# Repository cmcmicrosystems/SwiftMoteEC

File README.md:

# SwiftMote-Electrochemical Sensor Platform

## Acknowledgement

The hardware and software of the SwiftMoteEC was developed by CMC Microsystems in collaboration with Dr. Phillippe Dauphin Ducharme and his team at Université de Sherbrooke’s Department of Chemistry and Abaxial Medical, as part of the Acuité Québec Consortium.

---

 <br>
Figure 1: SwiftMoteEC Hardware Prototype
<br><br>

  <br>
Figure 2: SwiftMoteEC Block Diagram
<br><br>

SwiftMote-Electrochemical Sensor Platform is a small, wireless (BLE) platform designed for electrochemical experiments that require free movement of the sensing platform.

The platform features:
* ST BlueNRG-LP Bluetooth Low Energy microcontroller
  * 256kB flash memory
  * Expansion ports with 4x 12-bit ADC and I2C
* Analog Devices AD5941 potentiostat amplifer with 16-bit ADC and 12-bit DAC
* Host PC application to receive and store sensor data

The platform hardware and software are open and modifiable for end user applications. CMC has limited hardware samples available for demonstration and evaluation. Contact us for availability and pricing.

## Repository

This repo contains hardware design files and demonstration application software to manufacture the existing platform or modify it for specific user needs:
> /hardware : printed circuit board development and manufacturing of prototype hardware

> /software : demonstration application for Server (SwiftMoteEC) and Client (Windows PC)

## Getting Started

Instructions to setup and run a demonstration application is provided in the [software README.md](/software/README.md).

## Support

CMC can assist, from answering technical enquiries, to helping with installation and setup, to providing consulting services to customize the platform for your needs. If you have questions:

* Consult [Known_Issues.md](Known_Issues.md) for any outstanding technical notes and workarounds
* Submit an Issue in the repository
* CMC Subscribers: submit support questions through CMC's [Online Support Form](https://www.cmc.ca/support/)
* Contact [lab@cmc.ca](mailto:lab@cmc.ca) for further enquiries

## Additional Resources

[CMC SwiftMote Product Page](https://www.cmc.ca/swiftmote-iot-customizable-sensor-platform/)

For ST BlueNRG-LP:
* [Product information, documentation, and support](https://www.st.com/en/wireless-connectivity/bluenrg-lp.html)
* [Evaluation Tool Software](https://www.st.com/en/embedded-software/stsw-bnrglp-dk.html)

For Analog Devices AD5940/AD5941:
* [Product information, documentation, and support](https://www.analog.com/en/products/ad5940.html)
* [AD5940 Code Examples](https://github.com/analogdevicesinc/ad5940-examples)

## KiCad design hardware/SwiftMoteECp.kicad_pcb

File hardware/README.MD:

# Acknowledgement
The hardware and software of the SwiftMoteEC was developed by CMC Microsystems in collaboration with Dr. Phillippe Dauphin Ducharme and his team at Université de Sherbrooke’s Department of Chemistry and Abaxial Medical,  as part of the Acuité Québec Consortium.

# SwiftMoteECp_HW Repository
This repo is for development of the prototype hardware.  

Directories:  
> ./		: Project files including the schematic and printed circuit board  
>> /documentation	: A brief overview of power and programming  
>> /graphics	: A block diagram and photos of SwiftMote-Electrochemical  
>> /libraries     	: KiCad project related libraries including part symbols and footprints  
>> /licenses	: All hardware-related licenses  
>> /manufacturing	: All necessary files to manufacture the board.  Subdirectories include:  
>>>    /Bill_of_Materials : Bill of Materials (BoM) used to manufacture the first version of the board  
>>>    /Drill_Files	: Mechanical drill files  
>>>    /Instructions	: Special instructions to be provided to the board manufacturer  
>>>    /Plots	: Gerber files  
>>>    /Stackup	: Board stackup  
>>>    /XY_Position_Files : Orientation of the parts on the board  

Attention: 
1. Expansion header J2 was incorrectly specified (only 9-pins loaded, need all 10).  Change MPN FTSH-105-01-L-DV-007-P to FTSH-105-01-L-DV-P (Digikey PN# SAM8910-ND). You need to make this modification to the Bill of Materials before sending to manufacturing.
2. Capacitor C16 was changed to 10uF, MPN C0402C106M9PACTU , update the BoM.

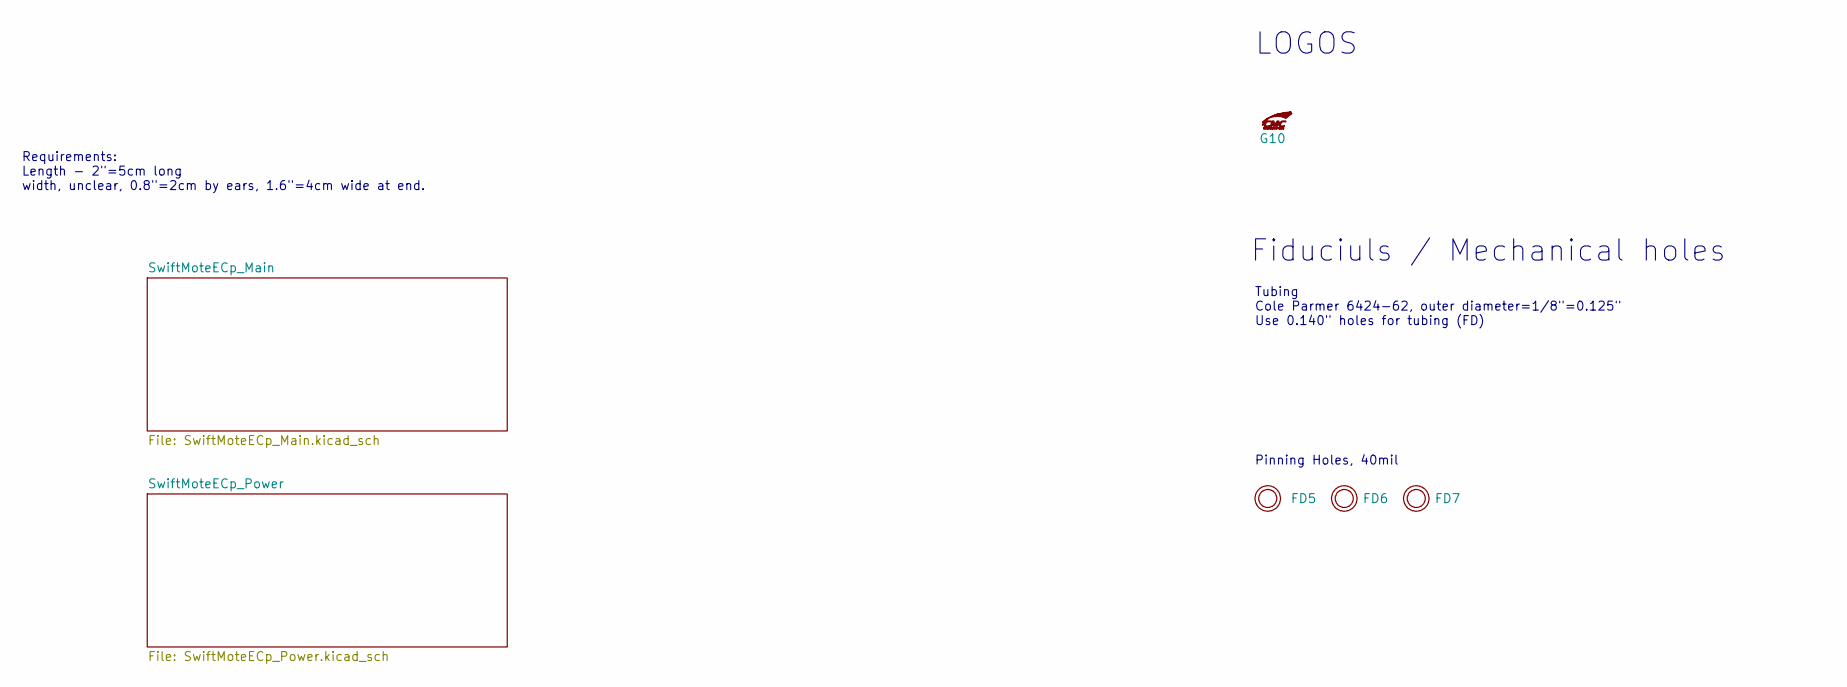
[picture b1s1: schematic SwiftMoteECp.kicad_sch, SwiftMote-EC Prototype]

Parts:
FD5, FD6, FD7: Pinning_NPTH_40mil
G10: CMC_White_Logo_180x110mil

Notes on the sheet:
Tubing Cole Parmer 6424-62, outer diameter=1/8"=0.125" Use 0.140" holes for tubing (FD)
Requirements: Length - 2"=5cm long width, unclear, 0.8"=2cm by ears, 1.6"=4cm wide at end.
LOGOS
Fiduciuls / Mechanical holes
Pinning Holes, 40mil

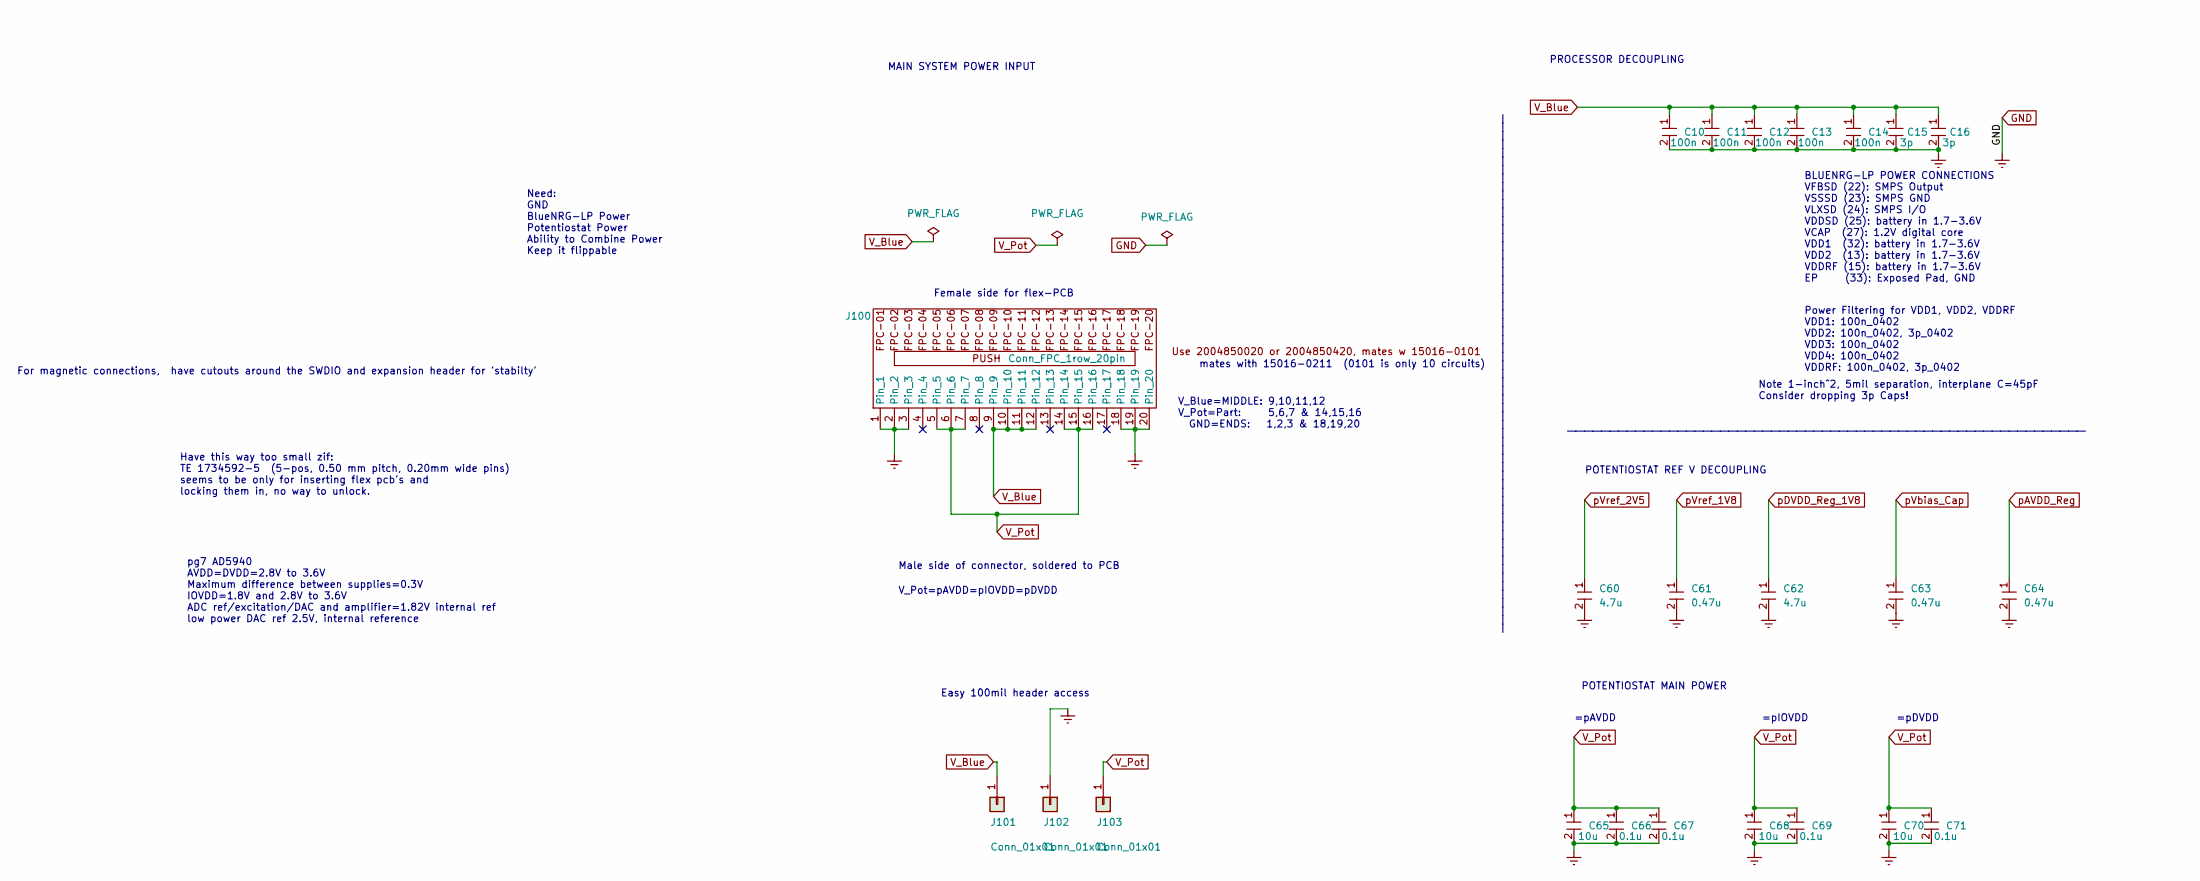
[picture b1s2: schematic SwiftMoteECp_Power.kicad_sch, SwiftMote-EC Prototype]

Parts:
C10, C11, C12, C13, C14: 100n; C_0402_1005Metric; Voltage 25V; Manufacturer PN GCM155R71E104KE02D; Digikey PN 490-16431-1-ND
C15, C16: 3p; C_0402_1005Metric; Voltage 50V; Manufacturer PN GCM1555C1H3R0BA16D; Digikey PN 490-14421-1-ND
C60, C62: 4.7u; C_0603_1608Metric; Voltage 16V; Manufacturer PN GRM188Z71C475KE21J; Digikey PN 490-GRM188Z71C475KE21JCT-ND
C61, C63, C64: 0.47u; C_0402_1005Metric; Voltage 10V; Manufacturer PN GRM155R71A474KE01D; Digikey PN 490-14366-1-ND
C65, C68: 10u; C_0805_2012Metric; Voltage 10V; Manufacturer PN GRM21BR71A106KA73L; Digikey PN 490-10516-1-ND
C66, C67, C69, C71: 0.1u; C_0402_1005Metric; Voltage 50V; Manufacturer PN GRM155R71H104KE14J; Digikey PN 490-13342-1-ND
C70: 10u; R_0805_2012Metric; Voltage 10V; Manufacturer PN GRM21BR71A106KA73L; Digikey PN 490-10516-1-ND
J100: Conn_FPC_1row_20pin; Molex_EasyOn_FFCFPC_2004850020; Manufacturer PN 2004850020; Digikey PN 900-2004850020TR-ND
J101, J102, J103: Conn_01x01; PinHeader_1x01_P2.54mm_Vertical; Manufacturer PN TSW-101-08-G-S; Digikey PN SAM1038-01-ND

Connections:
GND: C10.2, C11.2, C12.2, C13.2, C14.2, C15.2, C16.2, C60.2, C61.2, C62.2, C63.2, C64.2, C65.2, C66.2, C67.2, C68.2, C69.2, C70.2, C71.2, J100.1, J100.2, J100.3, J100.18, J100.19, J100.20, J102.1; also elsewhere on the board
V_Blue: C10.1, C11.1, C12.1, C13.1, C14.1, C15.1, C16.1, J100.9, J100.10, J100.11, J100.12, J101.1; also elsewhere on the board
V_Pot: C65.1, C66.1, C67.1, C68.1, C69.1, C70.1, C71.1, J100.5, J100.6, J100.7, J100.14, J100.15, J100.16, J103.1; also elsewhere on the board
pAVDD_Reg: C64.1; also elsewhere on the board
pDVDD_Reg_1V8: C62.1; also elsewhere on the board
pVbias_Cap: C63.1; also elsewhere on the board
pVref_1V8: C61.1; also elsewhere on the board
pVref_2V5: C60.1; also elsewhere on the board

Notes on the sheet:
Male side of connector, soldered to PCB
=pIOVDD
pg7 AD5940 AVDD=DVDD=2.8V to 3.6V Maximum difference between supplies=0.3V IOVDD=1.8V and 2.8V to 3.6V ADC ref/excitation/DAC and amplifier=1.82V internal ref low power DAC ref 2.5V, internal reference
_____________________________________________________________
Easy 100mil header access
Power Filtering for VDD1, VDD2, VDDRF VDD1: 100n_0402 VDD2: 100n_0402, 3p_0402 VDD3: 100n_0402 VDD4: 100n_0402 VDDRF: 100n_0402, 3p_0402
PROCESSOR DECOUPLING
Have this way too small zif: TE 1734592-5 (5-pos, 0.50 mm pitch, 0.20mm wide pins) seems to be only for inserting flex pcb's and locking them in, no way to unlock.
For magnetic connections, have cutouts around the SWDIO and expansion header for 'stabilty'
mates with 15016-0211 (0101 is only 10 circuits)
BLUENRG-LP POWER CONNECTIONS VFBSD (22): SMPS Output VSSSD (23): SMPS GND VLXSD (24): SMPS I/O VDDSD (25): battery in 1.7-3.6V VCAP (27): 1.2V digital core VDD1 (32): battery in 1.7-3.6V VDD2 (13): battery in 1.7-3.6V VDDRF (15): battery in 1.7-3.6V EP (33): Exposed Pad, GND
V_Blue=MIDDLE: 9,10,11,12 V_Pot=Part: 5,6,7 & 14,15,16 GND=ENDS: 1,2,3 & 18,19,20
Female side for flex-PCB
POTENTIOSTAT MAIN POWER
POTENTIOSTAT REF V DECOUPLING
=pDVDD
Note 1-inch^2, 5mil separation, interplane C=45pF Consider dropping 3p Caps!
V_Pot=pAVDD=pIOVDD=pDVDD
Need: GND BlueNRG-LP Power Potentiostat Power Ability to Combine Power Keep it flippable
=pAVDD
MAIN SYSTEM POWER INPUT

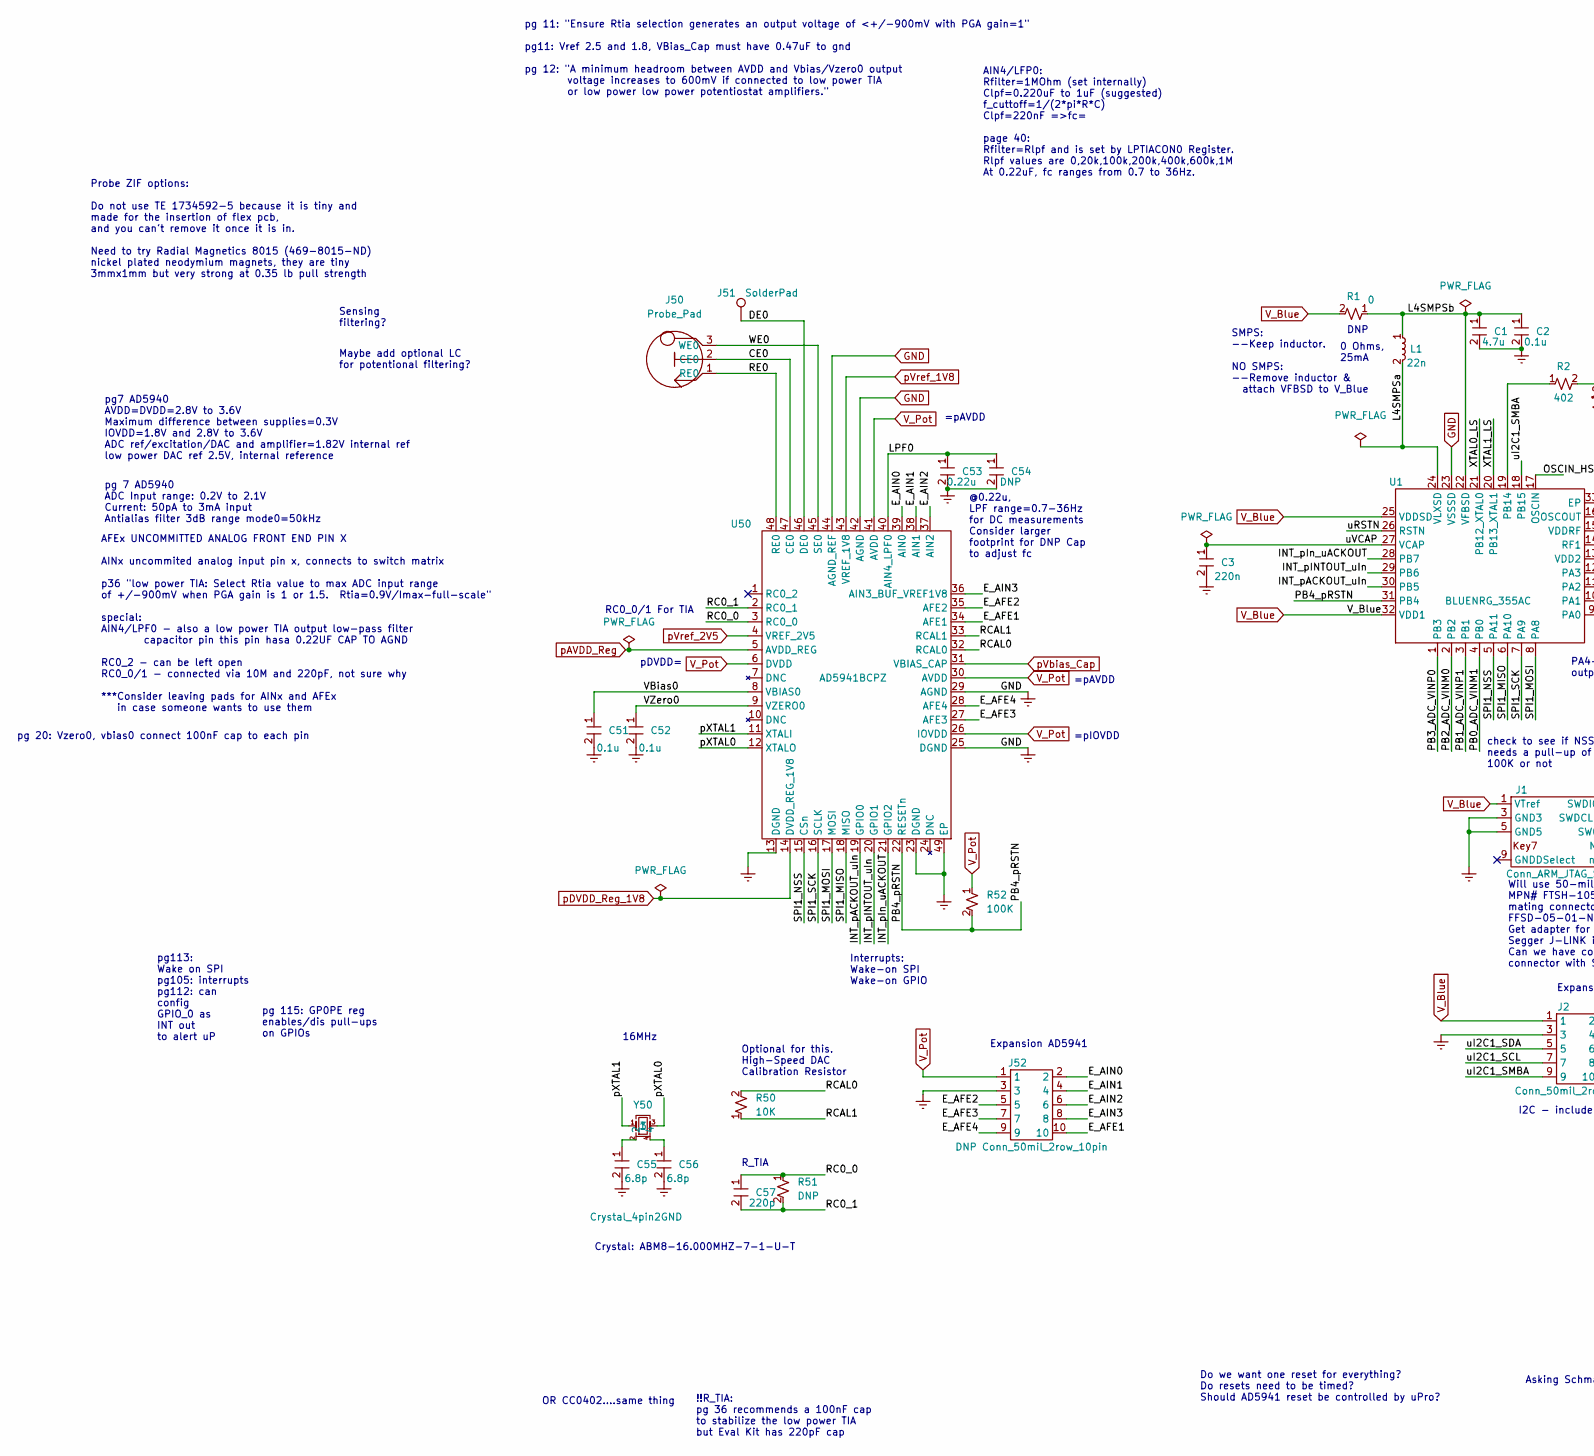
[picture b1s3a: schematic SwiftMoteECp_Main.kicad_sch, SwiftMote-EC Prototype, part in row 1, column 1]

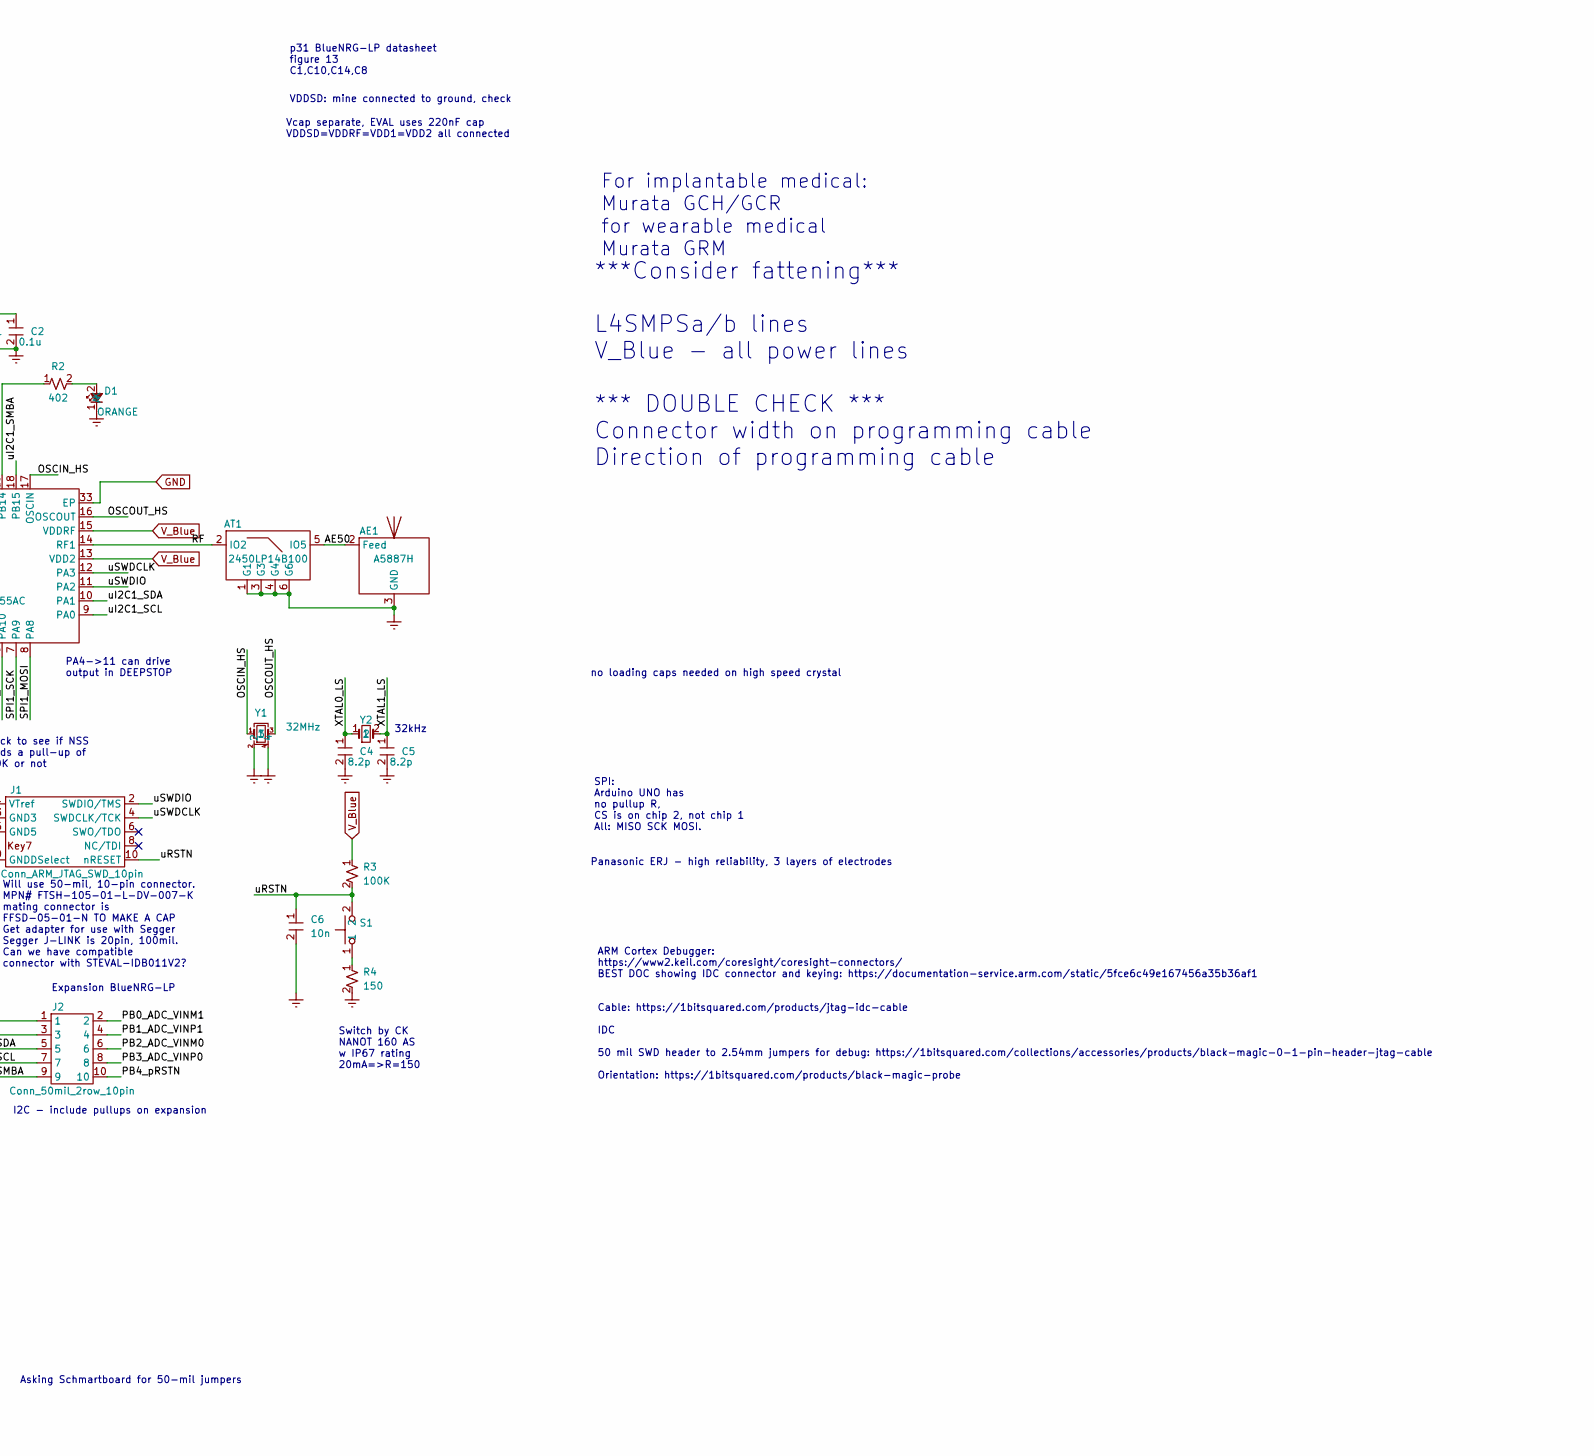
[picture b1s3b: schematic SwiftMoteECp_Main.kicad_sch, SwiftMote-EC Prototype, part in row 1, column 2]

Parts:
AE1: A5887H; RUFA_RT_A5887H; Manufacturer PN A5887H; Digikey PN 627-1127-1-ND
AT1: 2450LP14B100; JT_LPF_Bluetooth_2450LP14B100; Manufacturer PN 2450LP14B100T; Digikey PN 712-1130-1-ND
C1: 4.7u; C_0402_1005Metric; Voltage 16V; Manufacturer PN CL05A475MO5NUNC; Digikey PN 1276-6836-1-ND
C2, C51, C52: 0.1u; C_0402_1005Metric; Voltage 25V; Manufacturer PN C1005X7R1E104K050BB; Digikey PN 445-7348-1-ND
C3: 220n; R_0402_1005Metric; Voltage 25V; Manufacturer PN CGA2B3X7R1E224K050BB; Digikey PN 445-174424-1-ND
C4, C5: 8.2p; C_0201_0603Metric; Voltage 50V; Manufacturer PN GRM0335C1H8R2DA01D; Digikey PN 490-6133-1-ND
C6: 10n; C_0402_1005Metric; Voltage 25V; Manufacturer PN GRM1555C1E103GE01D; Digikey PN 490-GRM1555C1E103GE01DCT-ND
C53: 0.22u; C_0402_1005Metric_Pad0.74x0.62mm_HandSolder; Voltage 25V; Manufacturer PN GCM155R71C224KE02D; Digikey PN 490-10671-1-ND
C54: DNP; C_0402_1005Metric_Pad0.74x0.62mm_HandSolder; Voltage 25V; Manufacturer PN GCM155R71C224KE02D; Digikey PN 490-10671-1-ND
C55, C56: 6.8p; C_0402_1005Metric; Voltage 25V; Manufacturer PN C0402C689D3GAC7867; Digikey PN 399-15342-1-ND
C57: 220p; C_0402_1005Metric_Pad0.74x0.62mm_HandSolder; Voltage 25V; Manufacturer PN CC0402JRNPO8BN221; Digikey PN 311-1026-1-ND
D1: ORANGE; LED_0603_1608Metric_Pad1.05x0.95mm_HandSolder; Manufacturer PN XZCM2MOK53WA-1VF; Digikey PN 1497-XZCM2MOK53WA-1VFCT-ND
J1: Conn_ARM_JTAG_SWD_10pin; FTSH_10pin_2rows_50milPitch; Manufacturer PN FTSH-105-01-l-DV-007-K; Digikey PN SAM9438-ND
J2: Conn_50mil_2row_10pin; BlueExp_10pin_2rows_50milPitch; Manufacturer PN FTSH-105-01-l-DV-007-P; Digikey PN FTSH-105-01-L-DV-007-P-ND
J50: Probe_Pad; ProbePad_Magnetic_5x5mm; Manufacturer PN DNP; Digikey PN DNP
J51: SolderPad; Pad_5x5mm; Manufacturer PN DNP
J52: DNP Conn_50mil_2row_10pin; Conn_10pin_2rows_50milPitch; Manufacturer PN FTSH-105-01-l-DV-007-P; Digikey PN FTSH-105-01-L-DV-007-P-ND
L1: 22n; L_SMD_0402_1005Metric_Pad0.77x0.64mm_HandSolder; Manufacturer PN LQG15HS22NG02D; Digikey PN 490-LQG15HS22NG02DCT-ND
R1: 0; R_0402_1005Metric_Pad0.72x0.64mm_HandSolder; Manufacturer PN ERJ-U020R00X; Digikey PN 10-ERJ-U020R00XCT-ND
R2: 402; R_0402_1005Metric_Pad0.72x0.64mm_HandSolder; Manufacturer PN ERJ-2RKF4020X; Digikey PN P402LCT-ND
R3, R52: 100K; R_0402_1005Metric; Voltage 50V; Manufacturer PN CR0402-FX-1003GLF; Digikey PN CR0402-FX-1003GLFCT-ND
R4: 150; R_0402_1005Metric; Voltage 50V; Manufacturer PN ERJ-U02F1500X; Digikey PN 10-ERJ-U02F1500XCT-ND
R50: 10K; R_0603_1608Metric_Pad0.98x0.95mm_HandSolder; Voltage 75V; Tolerance 0.1%; Manufacturer PN ERA-3ARB103V; Digikey PN P10KBDCT-ND
R51: DNP; R_0402_1005Metric_Pad0.72x0.64mm_HandSolder
S1: Switch_SPST_NO; CuK_NanoT_AS; Manufacturer PN NANOT 160 AS; Digikey PN 108-NANOT160ASCT-ND
U1: BLUENRG_355AC; ST_BlueNRG_LP_QFN-32-1EP_5x5mm_P0.5mm_EP3.6x3.6mm; Manufacturer PN BLUENRG-355AT; Digikey PN 497-BLUENRG-355ATCT-ND
U50: AD5941BCPZ; AD5941BCPZ_LFCSP-48-1EP_7x7mm_P0.5mm_EP4.1x4.1mm; Manufacturer PN AD5941BCPZ; Digikey PN 505-AD5941BCPZ-ND
Y1: 32MHz; Crystal_SMD_2016-4Pin_2.0x1.6mm_sm; Manufacturer PN NX2016SA-32MHZ-EXS00A-CS11213; Digikey PN 644-1376-1-ND
Y2: Crystal_2pin; Crystal_SMD_2012-2Pin_2.0x1.2mm_sm; Manufacturer PN NX2012SA-32.768KHZ-EXS00A-MU00530; Digikey PN 644-1354-1-ND
Y50: Crystal_4pin2GND; Crystal_SMD_3225-4Pin_3.2x2.5mm; Manufacturer PN ABM8-16.000MHZ-7-1-U-T; Digikey PN 535-13466-1-ND

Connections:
/RatKit_Main/AE50: AE1.2 (Feed), AT1.5 (IO5)
/RatKit_Main/CE0: J50.2 (CE0), U50.47 (CE0)
/RatKit_Main/DE0: J51.1, U50.46 (DE0)
/RatKit_Main/E_AFE1: J52.10, U50.34 (AFE1)
/RatKit_Main/E_AFE2: J52.5, U50.35 (AFE2)
/RatKit_Main/E_AFE3: J52.7, U50.27 (AFE3)
/RatKit_Main/E_AFE4: J52.9, U50.28 (AFE4)
/RatKit_Main/E_AIN0: J52.2, U50.39 (AIN0)
/RatKit_Main/E_AIN1: J52.4, U50.38 (AIN1)
/RatKit_Main/E_AIN2: J52.6, U50.37 (AIN2)
/RatKit_Main/E_AIN3: J52.8, U50.36 (AIN3_BUF_VREF1V8)
/RatKit_Main/INT_pACKOUT_uIn: U1.30 (PB5), U50.19 (GPIO0)
/RatKit_Main/INT_pINTOUT_uIn: U1.29 (PB6), U50.20 (GPIO1)
/RatKit_Main/INT_pIn_uACKOUT: U1.28 (PB7), U50.21 (GPIO2)
/RatKit_Main/L4SMPSa: L1.2, U1.24 (VLXSD)
/RatKit_Main/L4SMPSb: C1.1, C2.1, L1.1, R1.1, U1.22 (VFBSD)
/RatKit_Main/LPF0: C53.1, C54.1, U50.40 (AIN4_LPF0)
/RatKit_Main/OSCIN_HS: U1.17 (OSCIN), Y1.1
/RatKit_Main/OSCOUT_HS: U1.16 (OSCOUT), Y1.3
/RatKit_Main/PB0_ADC_VINM1: J2.2, U1.4 (PB0)
/RatKit_Main/PB1_ADC_VINP1: J2.4, U1.3 (PB1)
/RatKit_Main/PB2_ADC_VINM0: J2.6, U1.2 (PB2)
/RatKit_Main/PB3_ADC_VINP0: J2.8, U1.1 (PB3)
/RatKit_Main/PB4_pRSTN: J2.10, R52.2, U1.31 (PB4), U50.22 (RESETn)
/RatKit_Main/RC0_0: C57.1, R51.1, U50.3 (RC0_0)
/RatKit_Main/RC0_1: C57.2, R51.2, U50.2 (RC0_1)
/RatKit_Main/RCAL0: R50.2, U50.32 (RCAL0)
/RatKit_Main/RCAL1: R50.1, U50.33 (RCAL1)
/RatKit_Main/RE0: J50.1 (RE0), U50.48 (RE0)
/RatKit_Main/RF: AT1.2 (IO2), U1.14 (RF1)
/RatKit_Main/SPI1_MISO: U1.6 (PA10), U50.18 (MISO)
/RatKit_Main/SPI1_MOSI: U1.8 (PA8), U50.17 (MOSI)
/RatKit_Main/SPI1_NSS: U1.5 (PA11), U50.15 (CSn)
/RatKit_Main/SPI1_SCK: U1.7 (PA9), U50.16 (SCLK)
/RatKit_Main/VBias0: C51.1, U50.8 (VBIAS0)
/RatKit_Main/VZero0: C52.1, U50.9 (VZERO0)
/RatKit_Main/WE0: J50.3 (WE0), U50.45 (SE0)
/RatKit_Main/XTAL0_LS: C4.1, U1.21 (PB12_XTAL0), Y2.1
/RatKit_Main/XTAL1_LS: C5.1, U1.20 (PB13_XTAL1), Y2.2
/RatKit_Main/pXTAL0: U50.12 (XTALO), Y50.3
/RatKit_Main/pXTAL1: U50.11 (XTALI), Y50.1
/RatKit_Main/uI2C1_SCL: J2.7, U1.9 (PA0)
/RatKit_Main/uI2C1_SDA: J2.5, U1.10 (PA1)
/RatKit_Main/uI2C1_SMBA: J2.9, U1.18 (PB15)
/RatKit_Main/uRSTN: C6.1, J1.10 (nRESET), R3.2, S1.2, U1.26 (RSTN)
/RatKit_Main/uSWDCLK: J1.4 (SWDCLK/TCK), U1.12 (PA3)
/RatKit_Main/uSWDIO: J1.2 (SWDIO/TMS), U1.11 (PA2)
/RatKit_Main/uVCAP: C3.1, U1.27 (VCAP)
GND: AE1.3 (GND), AT1.1 (G1), AT1.3 (G3), AT1.4 (G4), AT1.6 (G6), C1.2, C2.2, C3.2, C4.2, C5.2, C6.2, C51.2, C52.2, C53.2, C54.2, C55.2, C56.2, D1.1 (K), J1.3 (GND3), J1.5 (GND5), J2.3, J52.3, R4.2, U1.23 (VSSSD), U1.33 (EP), U50.13 (DGND), U50.23 (DGND), U50.25 (DGND), U50.29 (AGND), U50.42 (AGND), U50.44 (AGND_REF), U50.49 (EP), Y1.2, Y1.4; also elsewhere on the board
unnamed: C55.1, Y50.2
unnamed: C56.1, Y50.4
unnamed: D1.2 (A), R2.2
unnamed: R2.1, U1.19 (PB14)
unnamed: R4.1, S1.1
V_Blue: J1.1 (VTref), J2.1, R1.2, R3.1, U1.13 (VDD2), U1.15 (VDDRF), U1.25 (VDDSD), U1.32 (VDD1); also elsewhere on the board
V_Pot: J52.1, R52.1, U50.6 (DVDD), U50.26 (IOVDD), U50.30 (AVDD), U50.41 (AVDD); also elsewhere on the board
pAVDD_Reg: U50.5 (AVDD_REG); also elsewhere on the board
pDVDD_Reg_1V8: U50.14 (DVDD_REG_1V8); also elsewhere on the board
pVbias_Cap: U50.31 (VBIAS_CAP); also elsewhere on the board
pVref_1V8: U50.43 (VREF_1V8); also elsewhere on the board
pVref_2V5: U50.4 (VREF_2V5); also elsewhere on the board

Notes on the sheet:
Panasonic ERJ - high reliability, 3 layers of electrodes
RC0_0/1 For TIA
=pIOVDD
R_TIA
Crystal: ABM8-16.000MHZ-7-1-U-T
Do we want one reset for everything? Do resets need to be timed? Should AD5941 reset be controlled by uPro?
ARM Cortex Debugger: https://www2.keil.com/coresight/coresight-connectors/ BEST DOC showing IDC connector and keying: https://documentation-service.arm.com/static/5fce6c49e167456a35b36af1 Cable: https://1bitsquared.com/products/jtag-idc-cable IDC 50 mil SWD header to 2.54mm jumpers for debug: https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
***Consider fattening*** L4SMPSa/b lines V_Blue - all power lines *** DOUBLE CHECK *** Connector width on programming cable Direction of programming cable
Maybe add optional LC for potentional filtering?
no loading caps needed on high speed crystal
Will use 50-mil, 10-pin connector. MPN# FTSH-105-01-L-DV-007-K mating connector is FFSD-05-01-N TO MAKE A CAP Get adapter for use with Segger Segger J-LINK is 20pin, 100mil. Can we have compatible connector with STEVAL-IDB011V2?
Switch by CK NANOT 160 AS w IP67 rating 20mA=>R=150
pg 115: GP0PE reg enables/dis pull-ups on GPIOs
16MHz
AIN4/LFP0: Rfilter=1MOhm (set internally) Clpf=0.220uF to 1uF (suggested) f_cuttoff=1/(2*pi*R*C) Clpf=220nF =>fc= page 40: Rfilter=Rlpf and is set by LPTIACON0 Register. Rlpf values are 0,20k,100k,200k,400k,600k,1M At 0.22uF, fc ranges from 0.7 to 36Hz.
I2C - include pullups on expansion
Interrupts: Wake-on SPI Wake-on GPIO
SMPS: --Keep inductor. NO SMPS: --Remove inductor & attach VFBSD to V_Blue
Probe ZIF options: Do not use TE 1734592-5 because it is tiny and made for the insertion of flex pcb, and you can't remove it once it is in. Need to try Radial Magnetics 8015 (469-8015-ND) nickel plated neodymium magnets, they are tiny 3mmx1mm but very strong at 0.35 lb pull strength
PA4->11 can drive output in DEEPSTOP
=pAVDD
pg 11: "Ensure Rtia selection generates an output voltage of <+/-900mV with PGA gain=1" pg11: Vref 2.5 and 1.8, VBias_Cap must have 0.47uF to gnd pg 12: "A minimum headroom between AVDD and Vbias/Vzero0 output voltage increases to 600mV if connected to low power TIA or low power low power potentios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
Optional for this. High-Speed DAC Calibration Resistor
Expansion BlueNRG-LP
Sensing filtering?
OR CC0402....same thing
Expansion AD5941
VDDSD: mine connected to ground, check
p31 BlueNRG-LP datasheet figure 13 C1,C10,C14,C8
check to see if NSS needs a pull-up of 100K or not
AFEx UNCOMMITTED ANALOG FRONT END PIN X AINx uncommited analog input pin x, connects to switch matrix p36 "low power TIA: Select Rtia value to max ADC input range of +/-900mV when PGA gain is 1 or 1.5. Rtia=0.9V/Imax-full-scale" special: AIN4/LPF0 - also a low power TIA output low-pass filter capac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
0 Ohms, 25mA
!!R_TIA: pg 36 recommends a 100nF cap to stabilize the low power TIA but Eval Kit has 220pF cap
pg 7 AD5940 ADC Input range: 0.2V to 2.1V Current: 50pA to 3mA input Antialias filter 3dB range mode0=50kHz
pg 20: Vzero0, vbias0 connect 100nF cap to each pin
pg7 AD5940 AVDD=DVDD=2.8V to 3.6V Maximum difference between supplies=0.3V IOVDD=1.8V and 2.8V to 3.6V ADC ref/excitation/DAC and amplifier=1.82V internal ref low power DAC ref 2.5V, internal reference
Asking Schmartboard for 50-mil jumpers
Vcap separate, EVAL uses 220nF cap VDDSD=VDDRF=VDD1=VDD2 all connected
pDVDD=
32kHz

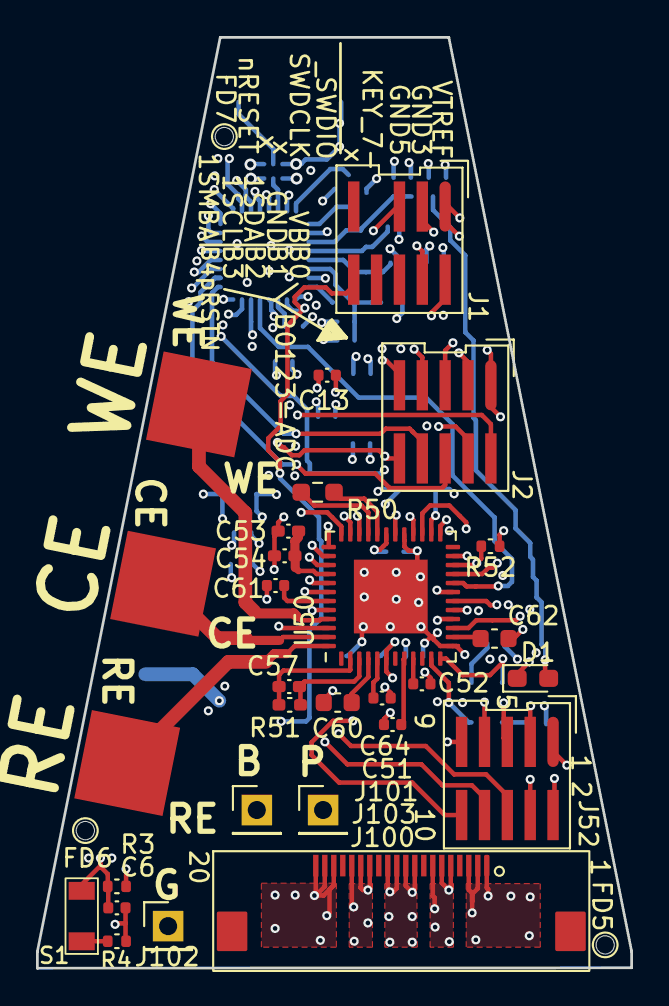
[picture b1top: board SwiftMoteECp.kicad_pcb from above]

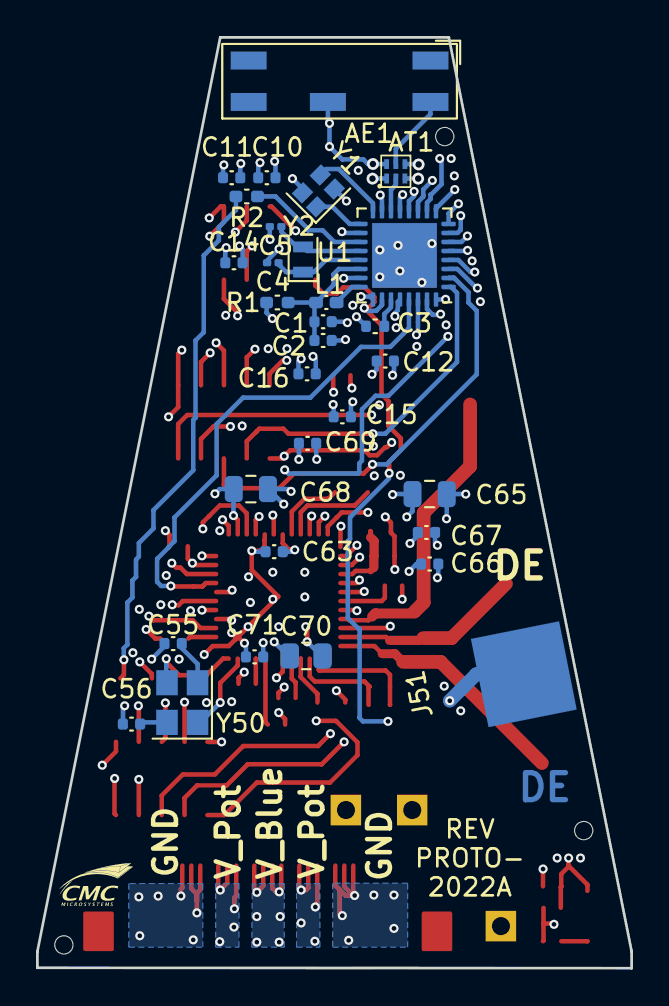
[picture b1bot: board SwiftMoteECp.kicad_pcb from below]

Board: 10 copper layers, 33.0 x 51.7 mm, 62 parts (32 on the bottom side), 61 nets.

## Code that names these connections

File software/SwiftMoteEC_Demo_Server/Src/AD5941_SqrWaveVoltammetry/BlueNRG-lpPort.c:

/**  
 * @file       BlueNRG-lpPort.c
 * @brief      CMC Microsystems SwiftMoteEC board port file.
 * @date       March 2023
 * @par Revision History: Derived from NUCLEOF411Port.c provided by Analog Devices
 *  
 * Copyright (c) 2017-2019 Analog Devices, Inc. All Rights Reserved. 
 * 
 * This software is proprietary to Analog Devices, Inc. and its licensors.
 * By using this software you agree to the terms of the associated
 * Analog Devices Software License Agreement.
**/

#include "ad5941.h"
#include "stdio.h"
#include "rf_driver_hal.h"
#include "swiftmoteEC_config.h"


/**
**Definition for BlueNRG-LP on SwiftMoteEC SPI clock resources when use SPI1.
**set clock source for each GPIO pins used.
**/

#define AD5941SPI                          SPI1
#define AD5941_CLK_ENABLE()                __HAL_RCC_SPI1_CLK_ENABLE()
#define AD5941_SCK_GPIO_CLK_ENABLE()       __HAL_RCC_GPIOA_CLK_ENABLE()   //PA9
#define AD5941_MISO_GPIO_CLK_ENABLE()      __HAL_RCC_GPIOA_CLK_ENABLE()  //PA10
#define AD5941_MOSI_GPIO_CLK_ENABLE()      __HAL_RCC_GPIOA_CLK_ENABLE() //PA8
#define AD5941_CS_GPIO_CLK_ENABLE()        __HAL_RCC_GPIOA_CLK_ENABLE() //PA11
#define AD5941_RST_GPIO_CLK_ENABLE()       __HAL_RCC_GPIOB_CLK_ENABLE()  //PB4
#define AD5941_GP0INT_GPIO_CLK_ENABLE()    __HAL_RCC_GPIOB_CLK_ENABLE() //PB5

#define AD5941SPI_FORCE_RESET()               __HAL_RCC_SPI1_FORCE_RESET()
#define AD5941SPI_RELEASE_RESET()             __HAL_RCC_SPI1_RELEASE_RESET()



/* Definition for AD5941 Pins that connects to BlueNRG-LP side */
#define AD5941_SCK_PIN                     GPIO_PIN_9
#define AD5941_SCK_GPIO_PORT               GPIOA
#define AD5941_SCK_AF                      GPIO_AF1_SPI1

#define AD5941_MISO_PIN                    GPIO_PIN_10
#define AD5941_MISO_GPIO_PORT              GPIOA
#define AD5941_MISO_AF                     GPIO_AF1_SPI1

#define AD5941_MOSI_PIN                    GPIO_PIN_8
#define AD5941_MOSI_GPIO_PORT              GPIOA
#define AD5941_MOSI_AF                     GPIO_AF1_SPI1

#define AD5941_CS_PIN                      GPIO_PIN_11
#define AD5941_CS_GPIO_PORT                GPIOA
#define AD5941_CS_AF											 GPIO_AF1_SPI1


#define AD5941_RST_PIN                     GPIO_PIN_4   //AD5941_RESET
#define AD5941_RST_GPIO_PORT               GPIOB

#define AD5941_GP0INT_PIN                  GPIO_PIN_5   // BlueNRG-LP take AD5941 interrupt input on GPIOA pin_5. 
#define AD5941_GP0INT_GPIO_PORT            GPIOB
#define AD5941_GP0INT_IRQn								 GPIOB_IRQn



SPI_HandleTypeDef  SpiHandle;

volatile static uint8_t ucInterrupted = 0;       /* Flag to indicate interrupt occurred */

/**
	@brief Using SPI to transmit N bytes and return the received bytes. This function targets to 
                     provide a more efficent way to transmit/receive data.
	@param pSendBuffer :{0 - 0xFFFFFFFF}
      - Pointer to the data to be sent.
	@param pRecvBuff :{0 - 0xFFFFFFFF}
      - Pointer to the buffer used to store received data.
	@param length :{0 - 0xFFFFFFFF}
      - Data length in SendBuffer.
	@return None.
**/
void AD5941_ReadWriteNBytes(unsigned char *pSendBuffer,unsigned char *pRecvBuff,unsigned long length)
{
  HAL_SPI_TransmitReceive(&SpiHandle, pSendBuffer, pRecvBuff, length, (uint32_t)-1);
}

void AD5941_CsClr(void)
{
  HAL_GPIO_WritePin(AD5941_CS_GPIO_PORT, AD5941_CS_PIN, GPIO_PIN_RESET);
}

void AD5941_CsSet(void)
{
  HAL_GPIO_WritePin(AD5941_CS_GPIO_PORT, AD5941_CS_PIN, GPIO_PIN_SET);
}

void AD5941_RstSet(void)
{
  HAL_GPIO_WritePin(AD5941_RST_GPIO_PORT, AD5941_RST_PIN, GPIO_PIN_SET);
}

void AD5941_RstClr(void)
{
  HAL_GPIO_WritePin(AD5941_RST_GPIO_PORT, AD5941_RST_PIN, GPIO_PIN_RESET);
}

void AD5941_Delay10us(uint32_t time)
{
  time/=100;
  if(time == 0) time =1;
  HAL_Delay(time);
}


uint32_t AD5941_GetMCUIntFlag(void)
{
	return ucInterrupted;
}

uint32_t AD5941_ClrMCUIntFlag(void)
{
	ucInterrupted = 0;
	return 1;
}


uint32_t AD5941_MCUResourceInit(void *pCfg)
{
	
	GPIO_InitTypeDef  GPIO_InitStruct;
  
  /* SPI SCK GPIO pin configuration */
  AD5941_SCK_GPIO_CLK_ENABLE();
  GPIO_InitStruct.Pin       = AD5941_SCK_PIN;
  GPIO_InitStruct.Mode      = GPIO_MODE_AF_PP;
  GPIO_InitStruct.Pull      = GPIO_PULLDOWN;
  GPIO_InitStruct.Speed     = GPIO_SPEED_FREQ_VERY_HIGH;
  GPIO_InitStruct.Alternate = AD5941_SCK_AF;
  HAL_GPIO_Init(AD5941_SCK_GPIO_PORT, &GPIO_InitStruct);
  
  /* SPI MISO GPIO pin configuration  */
	AD5941_MISO_GPIO_CLK_ENABLE();
  GPIO_InitStruct.Pin = AD5941_MISO_PIN;
	GPIO_InitStruct.Mode      = GPIO_MODE_AF_PP;
	GPIO_InitStruct.Pull      = GPIO_NOPULL;
	GPIO_InitStruct.Speed     = GPIO_SPEED_FREQ_VERY_HIGH;
  GPIO_InitStruct.Alternate = AD5941_MISO_AF;
  HAL_GPIO_Init(AD5941_MISO_GPIO_PORT, &GPIO_InitStruct);
  
  /* SPI MOSI GPIO pin configuration  */
	AD5941_MOSI_GPIO_CLK_ENABLE();
  GPIO_InitStruct.Pin = AD5941_MOSI_PIN;
	GPIO_InitStruct.Mode      = GPIO_MODE_AF_PP;
	GPIO_InitStruct.Pull      = GPIO_PULLDOWN;
	GPIO_InitStruct.Speed     = GPIO_SPEED_FREQ_VERY_HIGH;
  GPIO_InitStruct.Alternate = AD5941_MOSI_AF;
  HAL_GPIO_Init(AD5941_MOSI_GPIO_PORT, &GPIO_InitStruct);
  
	/* SPI CS GPIO pin configuration  */
	AD5941_CS_GPIO_CLK_ENABLE();
  GPIO_InitStruct.Pin = AD5941_CS_PIN;
	GPIO_InitStruct.Mode = GPIO_MODE_OUTPUT_PP;
  HAL_GPIO_Init(AD5941_CS_GPIO_PORT, &GPIO_InitStruct);
  
	AD5941_CLK_ENABLE();
	
  /* SPI RST GPIO pin configuration  */
	AD5941_RST_GPIO_CLK_ENABLE();
  GPIO_InitStruct.Pin = AD5941_RST_PIN;
  HAL_GPIO_Init(AD5941_RST_GPIO_PORT, &GPIO_InitStruct);
  
  AD5941_CsSet();
  AD5941_RstSet();
  
  /* Set the SPI parameters */
	
	SpiHandle.Instance               = AD5941SPI;
	SpiHandle.Init.Mode = SPI_MODE_MASTER;
	SpiHandle.Init.Direction         = SPI_DIRECTION_2LINES;
  SpiHandle.Init.CLKPolarity       = SPI_POLARITY_LOW;
  SpiHandle.Init.CLKPhase          = SPI_PHASE_1EDGE;
  SpiHandle.Init.DataSize          = SPI_DATASIZE_8BIT;
	//SpiHandle.Init.NSS               = SPI_NSS_SOFT;
	SpiHandle.Init.NSS               = SPI_NSS_HARD_OUTPUT;
	SpiHandle.Init.BaudRatePrescaler = SPI_BAUDRATEPRESCALER_8; //SPI clock should be < AD5941_SystemClock, system clock set for BlueNRG-LP is 64Mhz, therefore, SPI is 8MHz. AD5941 clock is set to 16Mhz in AD5941Main.c.
  SpiHandle.Init.FirstBit          = SPI_FIRSTBIT_MSB;
  SpiHandle.Init.TIMode            = SPI_TIMODE_DISABLE;
  SpiHandle.Init.CRCCalculation    = SPI_CRCCALCULATION_DISABLE;
  SpiHandle.Init.CRCPolynomial     = 7;
	
	SpiHandle.Init.CRCLength = SPI_CRC_LENGTH_DATASIZE;
  SpiHandle.Init.NSSPMode = SPI_NSS_PULSE_ENABLE;
  
  
  HAL_SPI_Init(&SpiHandle);
	__HAL_SPI_ENABLE(&SpiHandle);

	/* Step 2: Configure external interrupt line */
	
  AD5941_GP0INT_GPIO_CLK_ENABLE();
	
	LL_GPIO_SetPinMode(BSP_ad5941_INT_GPIO_PORT, BSP_ad5941_INT_PIN, LL_GPIO_MODE_INPUT);
  LL_GPIO_SetPinPull(BSP_ad5941_INT_GPIO_PORT, BSP_ad5941_INT_PIN, LL_GPIO_PULL_NO);
	
	LL_APB0_EnableClock(LL_APB0_PERIPH_SYSCFG);
	LL_EXTI_SetTrigger(BSP_ad5941_INT_EXTI_LINE_TRIGGER, BSP_ad5941_INT_EXTI_LINE);
  LL_EXTI_ClearInterrupt(BSP_ad5941_INT_EXTI_LINE);
  LL_EXTI_EnableIT(BSP_ad5941_INT_EXTI_LINE);
	

  NVIC_SetPriority(BSP_ad5941_INT_EXTI_IRQn, IRQ_LOW_PRIORITY);
  NVIC_EnableIRQ(BSP_ad5941_INT_EXTI_IRQn);

  return 0;
}

/* MCU related external line interrupt service routine */

void GPIOB_IRQHandler(void)
{
	ucInterrupted = 1;
  __HAL_GPIO_EXTI_CLEAR_IT(AD5941_GP0INT_GPIO_PORT,AD5941_GP0INT_PIN);
}

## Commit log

2024-02-13 Added LICENSE.md
2024-02-13 Cleaned private hardware repo, moved to public 13Feb2024 1:38PM
2024-02-13 Modified README.md file
2024-02-14 Modified README.md
2024-02-15 Modified README.md; added Block Diagram as png image
2024-02-20 Create Known_Issues.md
    Created a Known_Issues file. Combines H/W and S/W known issues with version number at the top.
2024-02-22 Fixed Known_Issues.md link in README
2024-02-22 added software directory
2024-02-22 Update Known_Issues.md
    Added software known issue.
2024-02-22 Update Known_Issues.md
    minor change on description of software known issue.
2024-03-07 updated application flow diagram on server side
2024-03-08 updated the flow application flow digram
2024-03-08 updated application flow diagram
2024-03-08 Update README.md
    Changed bleak installation command from:
    pip install bleak
    to
    pip install -U bleak
    -U is needed to force an update, otherwise a previous version would remain.
2024-03-12 Update README.md
    Updated README - step 5 in Server Demo Application section
2024-05-24 Minor correction of a name
2024-05-24 Minor correction of a name, take 2
2025-03-13 Corrected I/O configurations
